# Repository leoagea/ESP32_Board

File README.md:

# ESP32_Board
Homemade board with ESP32

This hardware design is licensed under the CERN-OHL-P v2.

You may use this design freely, modify it, and distribute it. 
If you distribute modified versions, you are encouraged but not required 
to publish them under the same licence.

For full details, see the LICENSE file or visit https://cern-ohl.web.cern.ch/.

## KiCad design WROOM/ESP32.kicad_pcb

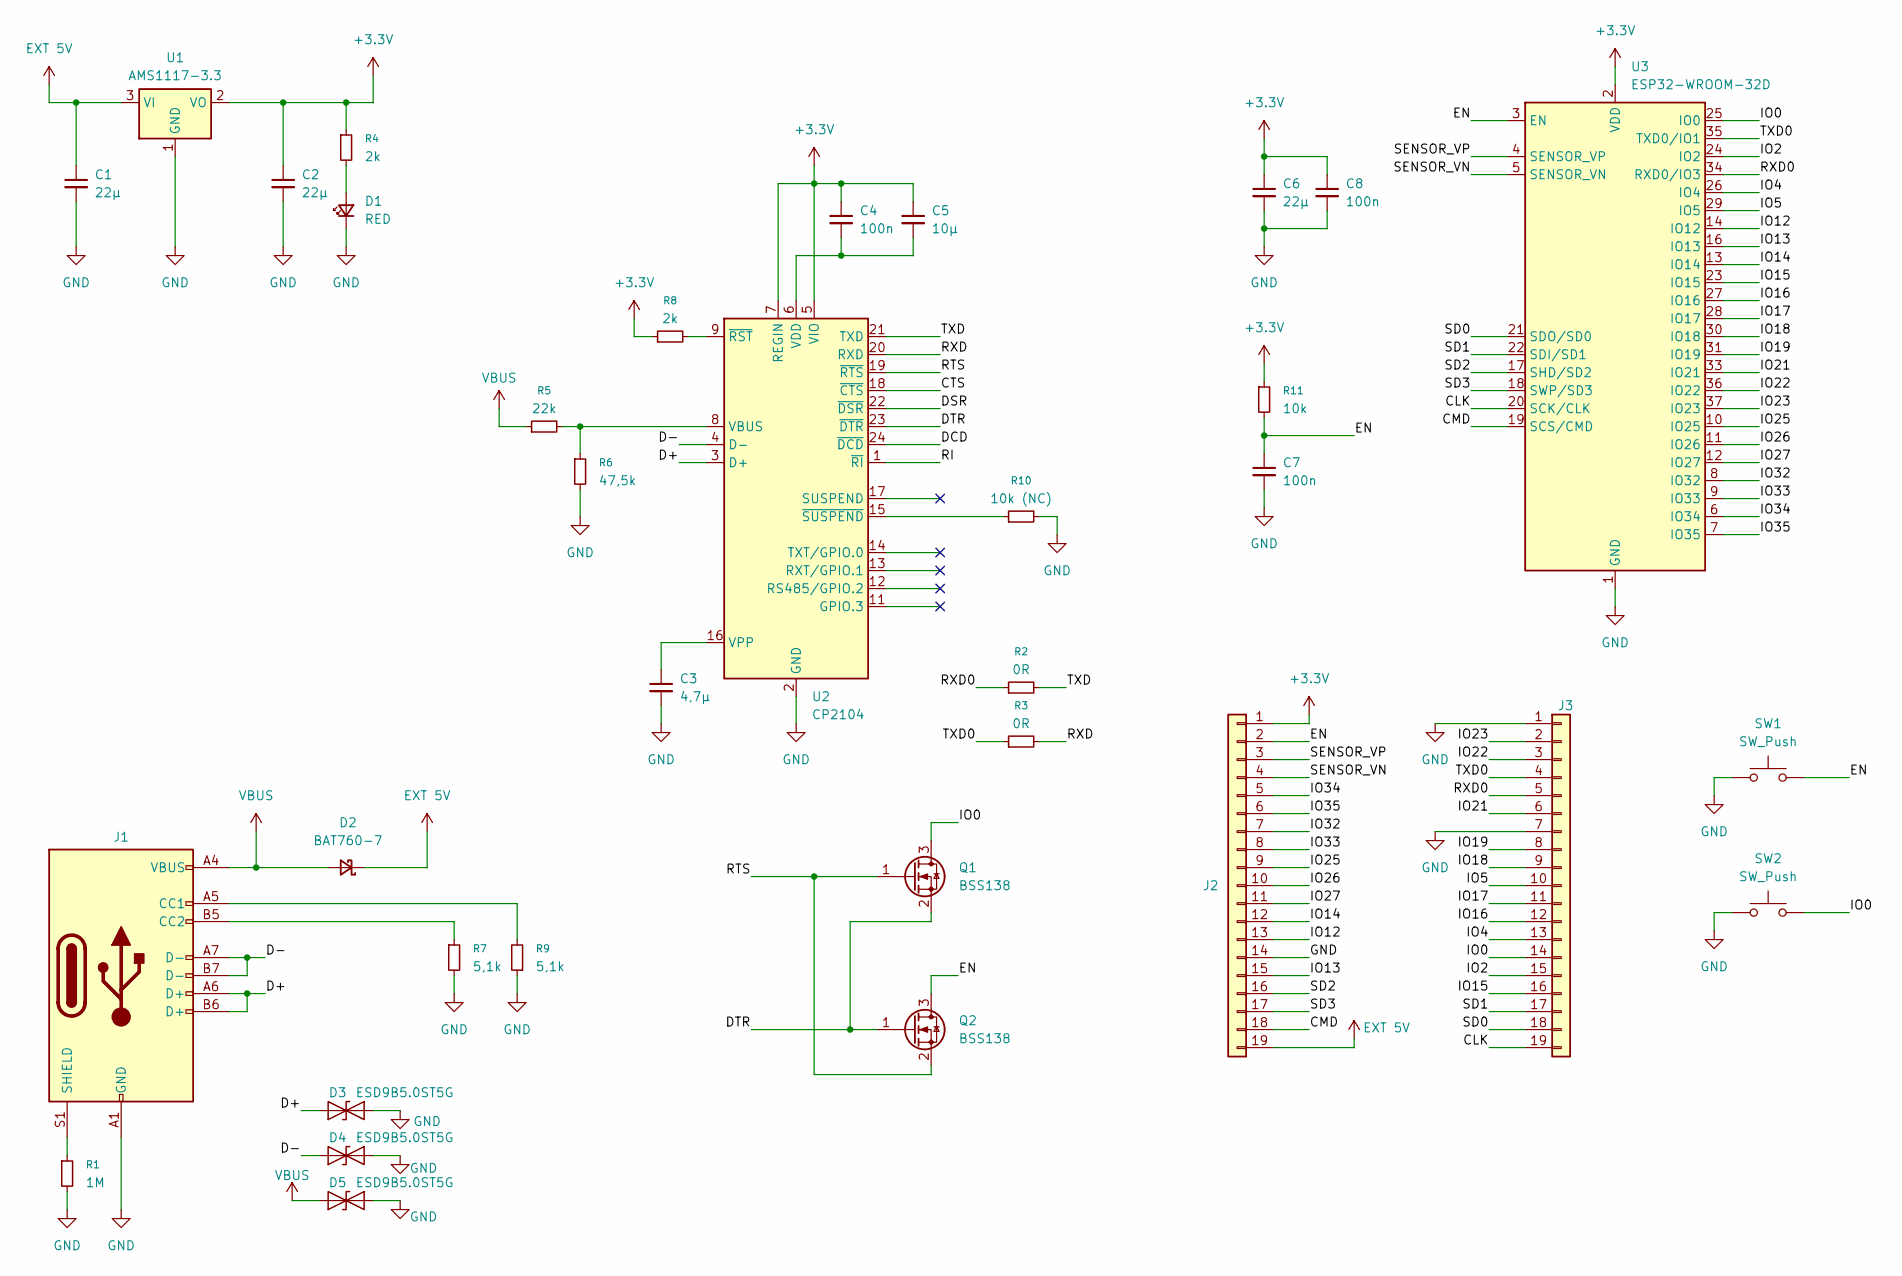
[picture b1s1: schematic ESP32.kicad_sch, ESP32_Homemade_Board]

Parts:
C1, C2, C6: 22µ; C_0603_1608Metric_Pad1.08x0.95mm_HandSolder; LCSC C86295
C3: 4,7µ; C_01005_0402Metric_Pad0.57x0.30mm_HandSolder; LCSC C23733
C4, C7, C8: 100n; C_01005_0402Metric_Pad0.57x0.30mm_HandSolder; LCSC C6119785
C5: 10µ; C_1206_3216Metric_Pad1.33x1.80mm_HandSolder; LCSC C127946
D1: RED; LED_0201_0603Metric; LCSC C19171390
D2: BAT760-7; D_SOD-323_HandSoldering; LCSC C27636120
D3, D4, D5: ESD9B5.0ST5G; D_SOD-923; LCSC C111566
J1: USB_C_Receptacle_USB2.0_14P; USB_C_Receptacle_GCT_USB4105-xx-A_16P_TopMnt_Horizontal; LCSC C2765186
J2, J3: Conn_01x19_Socket; PinHeader_1x19_P2.54mm_Vertical
Q1, Q2: BSS138; SOT-23_Handsoldering; LCSC C2874697
R1: 1M; R_01005_0402Metric_Pad0.57x0.30mm_HandSolder; LCSC C26083
R2, R3: 0R; R_0201_0603Metric_Pad0.64x0.40mm_HandSolder; LCSC C95177
R4, R8: 2k; R_0201_0603Metric_Pad0.64x0.40mm_HandSolder; LCSC C2907137
R5: 22k; R_0201_0603Metric_Pad0.64x0.40mm_HandSolder; LCSC C31850
R6: 47,5k; R_01005_0402Metric_Pad0.57x0.30mm_HandSolder; LCSC C2076913
R7, R9: 5,1k; R_0201_0603Metric_Pad0.64x0.40mm_HandSolder; LCSC C23186
R10: 10k (NC); LCSC C2930027
R11: 10k; R_0201_0603Metric_Pad0.64x0.40mm_HandSolder; LCSC C2930027
SW1, SW2: SW_Push; SW_Push_1P1T_NO_CK_KMR2; LCSC C49393608
U1: AMS1117-3.3; SOT-223; LCSC C347222
U2: CP2104; QFN-24-1EP_4x4mm_P0.5mm_EP2.5x2.5mm; LCSC C47742
U3: ESP32-WROOM-32D

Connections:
+3.3V: C2.1, C4.1, C5.1, C6.1, C8.1, J2.1, R4.1, R8.1, R11.1, U1.2 (VO), U2.5 (VIO), U2.7 (REGIN), U3.2 (VDD); also elsewhere on the board
/CLK: J3.19, U3.20 (SCK/CLK)
/CMD: J2.18, U3.19 (SCS/CMD)
/CTS: U2.18 (~CTS)
/D+: D3.2 (A2), J1.A6 (D+), J1.B6 (D+), U2.3 (D+)
/D-: D4.2 (A2), J1.A7 (D-), J1.B7 (D-), U2.4 (D-)
/DCD: U2.24 (~DCD)
/DSR: U2.22 (~DSR)
/DTR: Q1.2 (S), Q2.1 (G), U2.23 (~DTR)
/EN: C7.1, J2.2, Q2.3 (D), R11.2, SW1.2, U3.3 (EN)
/IO0: J3.14, Q1.3 (D), SW2.2, U3.25 (IO0)
/IO2: J3.15, U3.24 (IO2)
/IO4: J3.13, U3.26 (IO4)
/IO5: J3.10, U3.29 (IO5)
/IO12: J2.13, U3.14 (IO12)
/IO13: J2.15, U3.16 (IO13)
/IO14: J2.12, U3.13 (IO14)
/IO15: J3.16, U3.23 (IO15)
/IO16: J3.12, U3.27 (IO16)
/IO17: J3.11, U3.28 (IO17)
/IO18: J3.9, U3.30 (IO18)
/IO19: J3.8, U3.31 (IO19)
/IO21: J3.6, U3.33 (IO21)
/IO22: J3.3, U3.36 (IO22)
/IO23: J3.2, U3.37 (IO23)
/IO25: J2.9, U3.10 (IO25)
/IO26: J2.10, U3.11 (IO26)
/IO27: J2.11, U3.12 (IO27)
/IO32: J2.7, U3.8 (IO32)
/IO33: J2.8, U3.9 (IO33)
/IO34: J2.5, U3.6 (IO34)
/IO35: J2.6, U3.7 (IO35)
/RI: U2.1 (~RI)
/RTS: Q1.1 (G), Q2.2 (S), U2.19 (~RTS)
/RXD: R3.2, U2.20 (RXD)
/RXD0: J3.5, R2.1, U3.34 (RXD0/IO3)
/SD0: J3.18, U3.21 (SDO/SD0)
/SD1: J3.17, U3.22 (SDI/SD1)
/SD2: J2.16, U3.17 (SHD/SD2)
/SD3: J2.17, U3.18 (SWP/SD3)
/SENSOR_VN: J2.4, U3.5 (SENSOR_VN)
/SENSOR_VP: J2.3, U3.4 (SENSOR_VP)
/TXD: R2.2, U2.21 (TXD)
/TXD0: J3.4, R3.1, U3.35 (TXD0/IO1)
EXT 5V: C1.1, D2.1 (K), J2.19, U1.3 (VI); also elsewhere on the board
GND: C1.2, C2.2, C3.2, C6.2, C7.2, C8.2, D1.1 (K), D3.1 (A1), D4.1 (A1), D5.1 (A1), J1.A1 (GND), J1.A12 (GND), J1.B1 (GND), J1.B12 (GND), J2.14, J3.1, J3.7, R1.2, R6.2, R7.2, R9.1, R10.2, SW1.1, SW2.1, U1.1 (GND), U2.2 (GND), U2.25 (GND), U3.1 (GND), U3.15 (GND), U3.38 (GND), U3.39 (GND); also elsewhere on the board
unnamed: D1.2 (A), R4.2
unnamed: J1.A5 (CC1), R9.2
unnamed: J1.B5 (CC2), R7.1
unnamed: J1.S1 (SHIELD), R1.1
unnamed: R5.2, R6.1, U2.8 (VBUS)
unnamed: C4.2, C5.2, U2.6 (VDD)
unnamed: C3.1, U2.16 (VPP)
unnamed: R8.2, U2.9 (~RST)
unnamed: R10.1, U2.15 (~SUSPEND)
VBUS: D2.2 (A), D5.2 (A2), J1.A4 (VBUS), J1.A9 (VBUS), J1.B4 (VBUS), J1.B9 (VBUS), R5.1

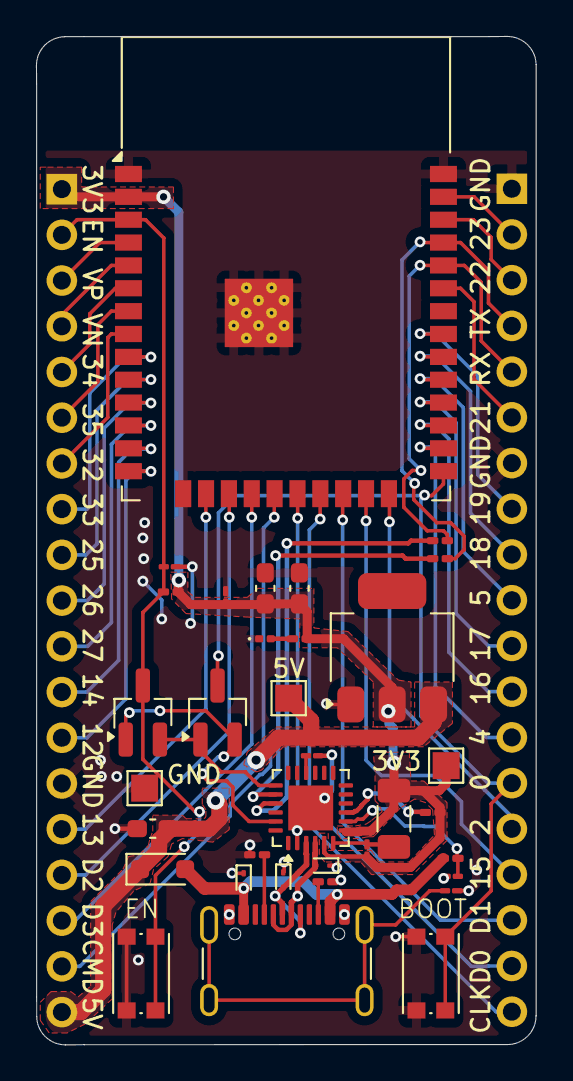
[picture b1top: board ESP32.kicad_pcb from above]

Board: 2 copper layers, 27.8 x 56.0 mm, 36 parts (0 on the bottom side), 51 nets.

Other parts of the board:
3V3, 5V: TestPoint_Pad_1.5x1.5mm
GND: TestPoint_Pad_1.5x1.5mm

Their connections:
+3.3V: 3V3.1; also elsewhere on the board
EXT 5V: 5V.1; also elsewhere on the board
GND: GND.1; also elsewhere on the board

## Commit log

2026-01-21 Add license
2026-01-26 CP2104, ESP32 3D models
2026-01-27 Moove to WROOM dir
2026-01-27 Add gerbers files
2026-01-28 S3-mini v1
